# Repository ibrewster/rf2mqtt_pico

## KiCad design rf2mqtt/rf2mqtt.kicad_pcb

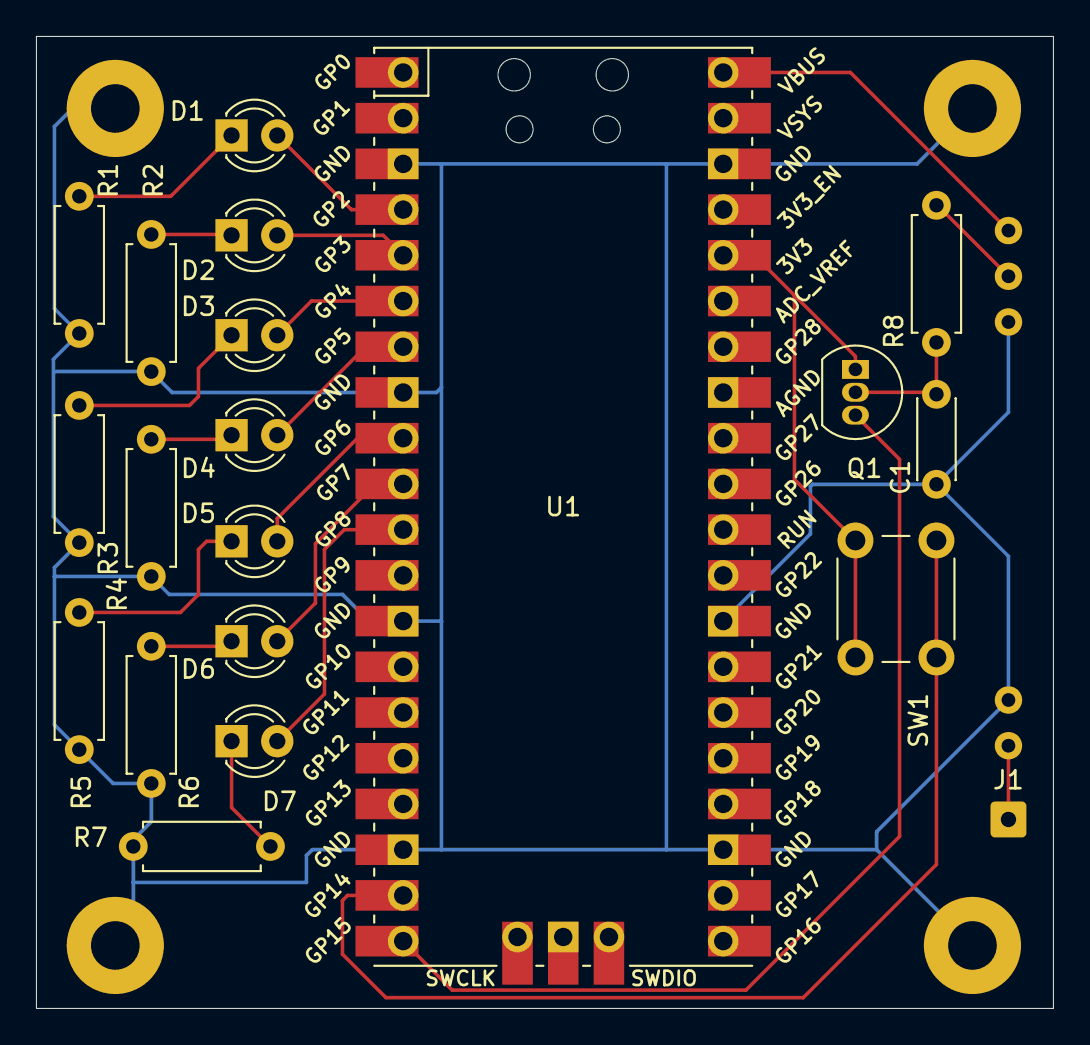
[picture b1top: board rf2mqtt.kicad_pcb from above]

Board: 2 copper layers, 56.5 x 54.0 mm, 25 parts (0 on the bottom side), 22 nets.

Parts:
C1: C; C_Disc_D4.3mm_W1.9mm_P5.00mm
D1, D2, D3, D4, D5, D6, D7: LED; LED_D3.0mm
J1: Antenna Wire; SolderWire-0.25sqmm_1x01_D0.65mm_OD2mm
Q1: TN0106N3-G; TO-92_Inline
R1, R2, R3, R4, R5, R6, R7: 680; R_Axial_DIN0207_L6.3mm_D2.5mm_P7.62mm_Horizontal
R8: 10kΩ; R_Axial_DIN0207_L6.3mm_D2.5mm_P7.62mm_Horizontal
REF1, REF1#2, REF1#3, REF1#4: MountingHole_2.7mm_M2.5_Pad
RF1: SH_RF_RECIEVER
SW1: config; SW_PUSH_6mm_H13mm
U1: Pico; RPi_Pico_SMD_TH

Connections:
+5V: RF1.1 (+5V), U1.40 (VBUS)
GND: C1.2, R1.1, R2.1, R3.1, R4.1, R5.1, R6.1, R7.1, REF1.1, REF1#2.1, REF1#3.1, REF1#4.1, RF1.3 (GND), RF1.4 (GND), U1.3 (GND), U1.8 (GND), U1.13 (GND), U1.18 (GND), U1.23 (GND), U1.28 (GND), U1.38 (GND)
unnamed: D1.2 (A), U1.4 (GPIO2)
unnamed: D1.1 (K), R1.2
unnamed: D2.2 (A), U1.5 (GPIO3)
unnamed: D2.1 (K), R2.2
unnamed: D3.2 (A), U1.6 (GPIO4)
unnamed: D3.1 (K), R3.2
unnamed: D4.2 (A), U1.7 (GPIO5)
unnamed: D4.1 (K), R4.2
unnamed: D5.2 (A), U1.9 (GPIO6)
unnamed: D5.1 (K), R5.2
unnamed: D6.2 (A), U1.10 (GPIO7)
unnamed: D6.1 (K), R6.2
unnamed: D7.2 (A), U1.11 (GPIO8)
unnamed: D7.1 (K), R7.2
unnamed: J1.1, RF1.5 (ANT)
unnamed: Q1.3 (D), U1.20 (GPIO15)
unnamed: C1.1, Q1.2 (G), R8.1
unnamed: Q1.1 (S), SW1.1, U1.36 (3V3)
unnamed: R8.2, RF1.2 (DATA)
unnamed: SW1.2, U1.19 (GPIO14)

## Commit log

2024-05-25 Inital commit of files
2024-05-27 Move MQTT code to a more generic utils.py file that can be used from anywhere Better debounce push button input Add "factory reset"
2024-05-30 Code cleanup, prevent browsers from suggesting a password (auto-fill only), and add KiCad drawings
2024-06-19 Add debug MQTT messages
2024-06-19 Add WiFi watchdog/reconnect logic
2024-06-22 Use hardware timers for LED blink to work around asyncio limitations and allow a nice long sleep cycle for the main loop.
